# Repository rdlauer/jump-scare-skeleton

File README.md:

# Remotely Terrorize the Neighborhood Kids on Halloween

This IoT project uses a Notecard to build a remotely-triggered jump-scare skeleton without using a host MCU on the skeleton.

See the full project writeup [on Hackster](https://www.hackster.io/rob-lauer/remotely-terrorize-the-neighborhood-kids-on-halloween-6b9f41)!

This project uses...

- [Blues Wireless Notecard](https://blues.io/products/notecard/)
- [Blues Wireless Notecarrier-A](https://blues.io/products/notecarrier/notecarrier-a/)
- [Blues Wireless Swan](https://blues.io/products/swan/)

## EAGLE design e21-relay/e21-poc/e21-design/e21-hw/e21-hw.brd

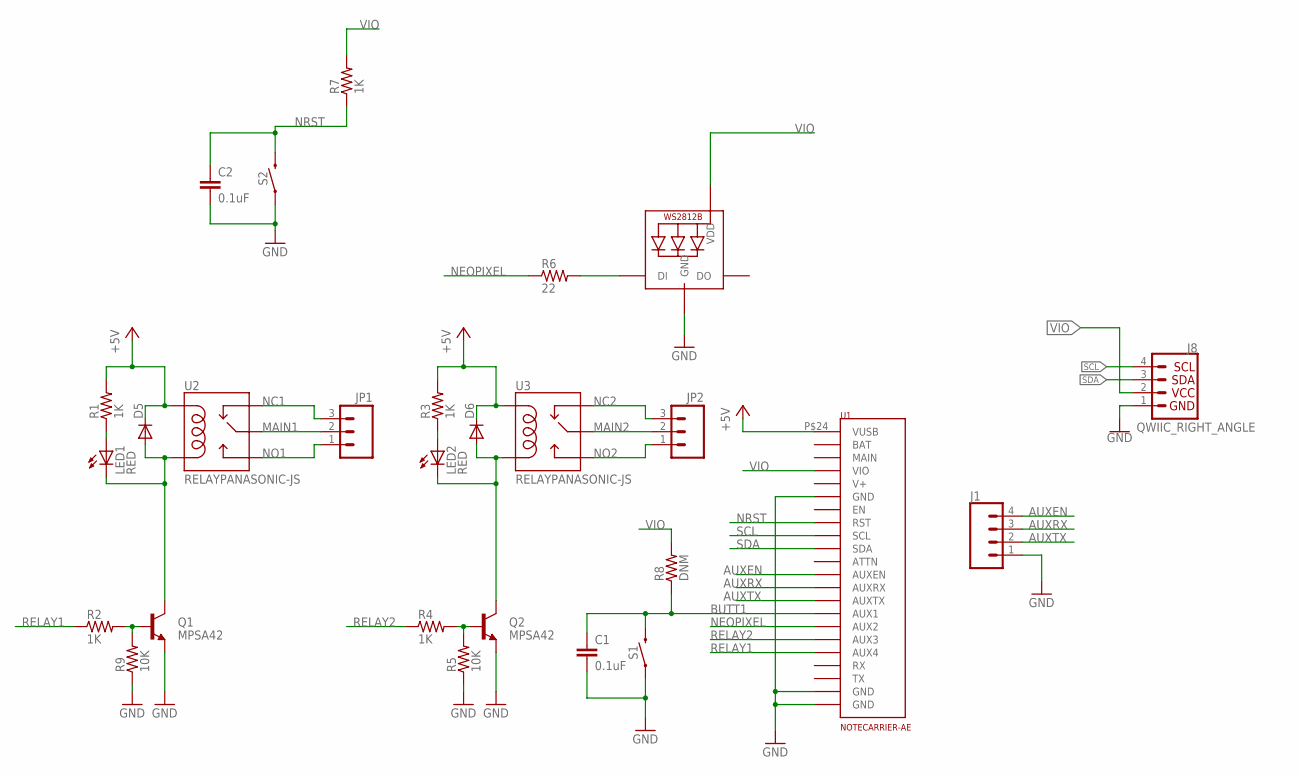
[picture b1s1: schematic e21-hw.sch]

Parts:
C1, C2: 0.1uF; 0603
D5, D6: DIODE-SOD123; SOD123
J1: CONN_04LOCK; 1X04_LOCK
J8: QWIIC_RIGHT_ANGLE; JST04_1MM_RA
JP1, JP2: M03-SCREW-5MM; SCREWTERMINAL-5MM-3
LED1, LED2: RED; LED-0603
LED3: WS2812B5050; WS2812B
Q1, Q2: MPSA42; SOT23
R1, R2, R3, R4, R7: 1K; 0603-RES
R5, R9: 10K; 0603-RES
R6: 22; 0603-RES
R8: DNM; 0603-RES
S1, S2: MOMENTARY-SWITCH-SPST-PTH-6.0MM; TACTILE_SWITCH_PTH_6.0MM
U1: NOTECARRIER-AE
U2, U3: RELAYPANASONIC-JS; JS1-5V-F

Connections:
+5V: D5.C, D6.C, R1.2, R3.2, U1.P$24 (VUSB), U2.COIL1, U3.COIL1
AUXEN: J1.4, U1.P$11 (AUXEN)
AUXRX: J1.3, U1.P$10 (AUXRX)
AUXTX: J1.2, U1.P$9 (AUXTX)
BUTT1: C1.1, R8.1, S1.3 (2), U1.P$8 (AUX1)
GND: C1.2, C2.2, J1.1, J8.1, LED3.3-GND (GND), Q1.2 (E), Q2.2 (E), R5.1, R9.1, S1.1, S2.1, U1.P$1 (GND), U1.P$2 (GND), U1.P$18 (GND)
MAIN1: JP1.2, U2.COMMON (MAIN)
MAIN2: JP2.2, U3.COMMON (MAIN)
unnamed: D5.A, LED1.C, Q1.3 (C), U2.COIL2
unnamed: Q2.1 (B), R4.2, R5.2
unnamed: Q1.1 (B), R2.2, R9.2
unnamed: LED1.A, R1.1
unnamed: D6.A, LED2.C, Q2.3 (C), U3.COIL2
unnamed: LED2.A, R3.1
unnamed: LED3.4-DIN (DI), R6.2
NC1: JP1.3, U2.CLOSED (NC)
NC2: JP2.3, U3.CLOSED (NC)
NEOPIXEL: R6.1, U1.P$7 (AUX2)
NO1: JP1.1, U2.OPEN (NO)
NO2: JP2.1, U3.OPEN (NO)
NRST: C2.1, R7.1, S2.3 (2), U1.P$16 (RST)
RELAY1: R2.1, U1.P$5 (AUX4)
RELAY2: R4.1, U1.P$6 (AUX3)
SCL: J8.4, U1.P$14 (SCL)
SDA: J8.3, U1.P$13 (SDA)
VIO: J8.2, LED3.1-VDD (VDD), R7.2, R8.2, U1.P$21 (VIO)

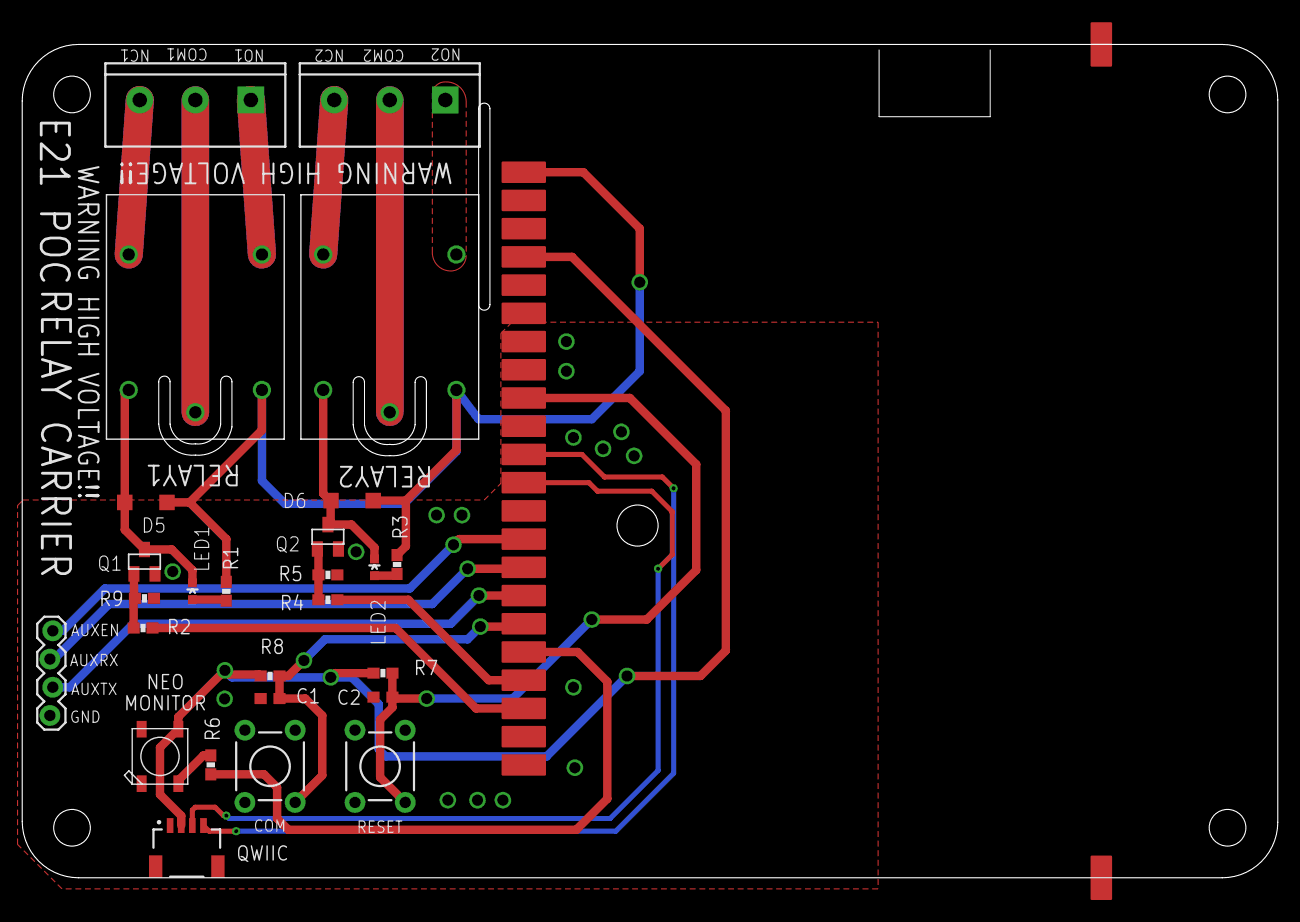
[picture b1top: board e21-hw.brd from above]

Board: 2 copper layers, 113.0 x 75.0 mm, 27 parts (0 on the bottom side), 26 nets.

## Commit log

2022-10-21 add gif
2022-10-21 removing skeleton gif
2022-10-21 add hackster link

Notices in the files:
parts and their libraries:
SparkFun-Connectors: Licensing: CC v3.0 Share-Alike You are welcome to use this library for commercial purposes.
SparkFun-Switches: Licensing: Creative Commons ShareAlike 4.0 International - https://creativecommons.org/licenses/by-sa/4.0
